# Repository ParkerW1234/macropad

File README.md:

<h1>Hackpad</h1>

<p>
A simple <strong>5-key macropad</strong> built with a <strong>Seeed XIAO RP2040</strong> and a <strong>0.91&quot; OLED display</strong>.
</p>

<p>
Designed as a small, programmable USB macropad.
</p>

<hr>

<h2>Features</h2>

<ul>
  <li>5 mechanical keys (direct GPIO wiring)</li>
  <li>0.91&quot; I²C OLED display</li>
  <li>USB HID keyboard</li>
  <li>Programmable macros</li>
  <li>Custom PCB (KiCad)</li>
</ul>

<hr>

<h2>Hardware</h2>

<ul>
  <li>Seeed XIAO RP2040</li>
  <li>5× MX-style switches</li>
  <li>0.91&quot; OLED display (GND–VCC–SCL–SDA pin order)</li>
  <li>M3x5mx4mm heatset inserts</li>
  <li>M3x16mm screws</li>
</ul>

<hr>

<h2>Firmware</h2>

<ul>
  <li>Written in CircuitPython</li>
  <li>Acts as a USB keyboard</li>
  <li>Displays simple text/status on the OLED</li>
</ul>

<p>
Main firmware file:
</p>

<pre><code>firmware/main.py</code></pre>

<hr>

<h2>Installation</h2>

<ol>
  <li>Flash CircuitPython to the Seeed XIAO RP2040</li>
  <li>Copy required libraries to <code>CIRCUITPY/lib</code></li>
  <li>Copy <code>main.py</code> to the board</li>
</ol>

<hr>

<h2>PCB</h2>

<ul>
  <li>Designed in KiCad</li>
  <li>Keys wired directly to GPIO pins</li>
  <li>OLED connected over I²C (SDA/SCL)</li>
</ul>

<hr>

<h2>Case</h2>

<p>
The PCB fits inside a simple case that is secured with the M3x5mx4mm heatset inserts and m3x16 mm screws.

<hr>

<h2>My PCB</h2>

<hr>

<h2>My Schematic</h2>

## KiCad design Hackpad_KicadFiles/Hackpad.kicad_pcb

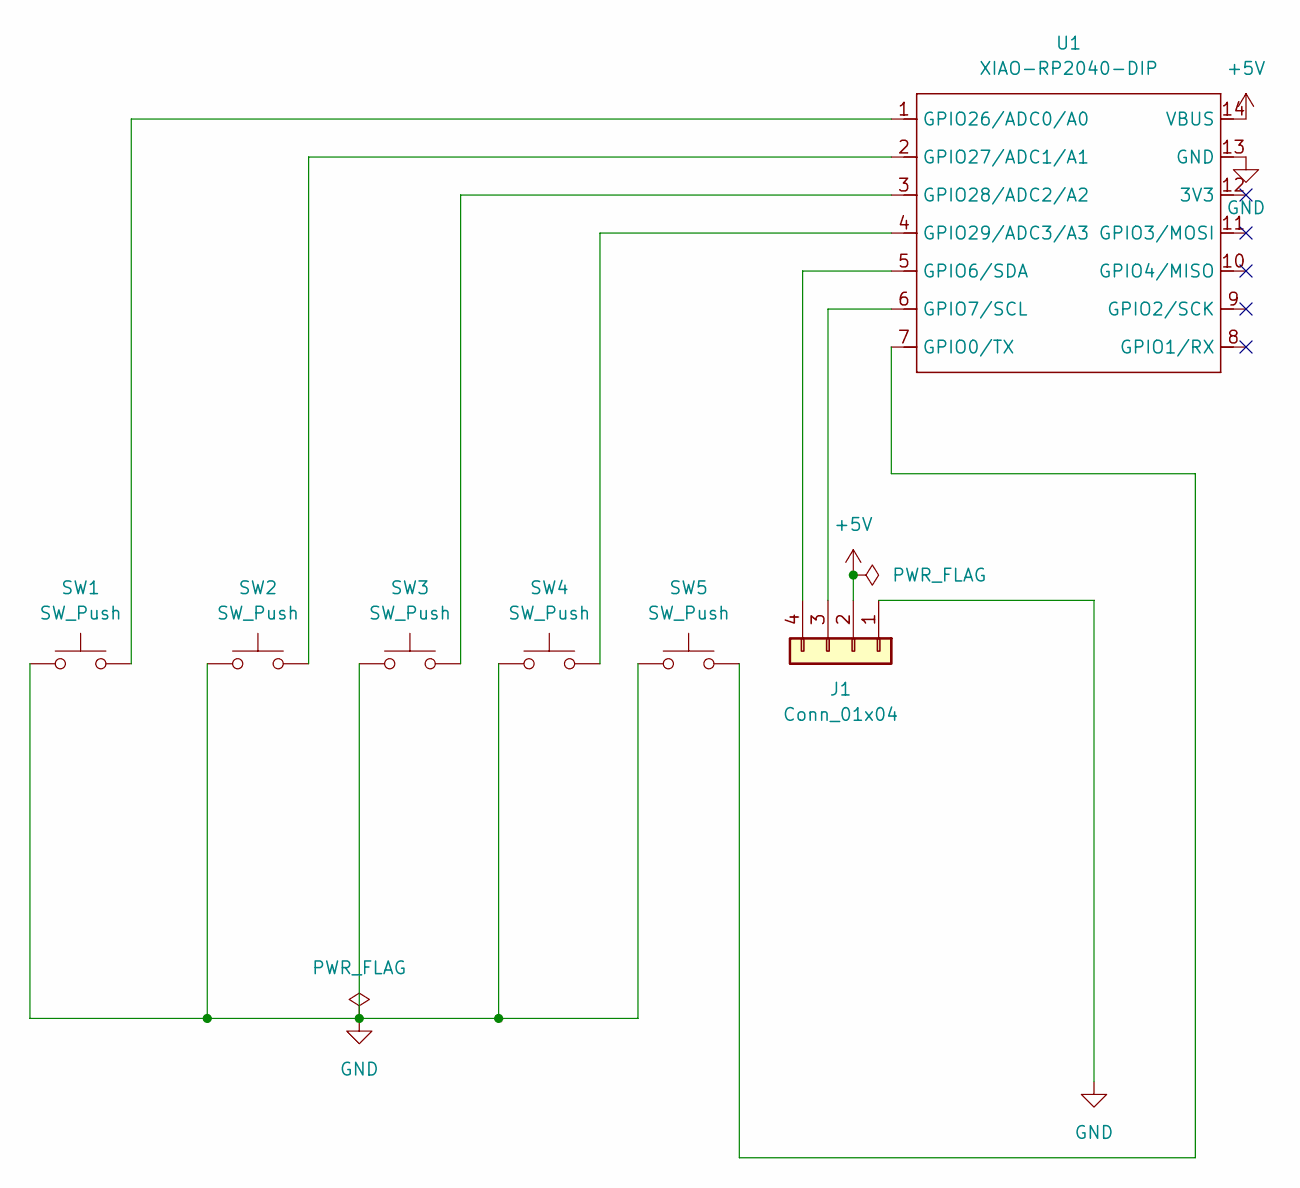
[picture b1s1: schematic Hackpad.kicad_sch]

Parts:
J1: Conn_01x04; PinSocket_1x04_P2.54mm_Vertical
SW1, SW2, SW3, SW4, SW5: SW_Push; SW_Cherry_MX_1.00u_PCB
U1: XIAO-RP2040-DIP; XIAO-ESP32C3-DIP

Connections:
+5V: J1.2, U1.14 (VBUS)
GND: J1.1, SW1.1, SW2.1, SW3.1, SW4.1, SW5.1, U1.13 (GND)
unnamed: J1.3, U1.6 (GPIO7/SCL)
unnamed: J1.4, U1.5 (GPIO6/SDA)
unnamed: SW5.2, U1.7 (GPIO0/TX)
unnamed: SW1.2, U1.1 (GPIO26/ADC0/A0)
unnamed: SW2.2, U1.2 (GPIO27/ADC1/A1)
unnamed: SW3.2, U1.3 (GPIO28/ADC2/A2)
unnamed: SW4.2, U1.4 (GPIO29/ADC3/A3)

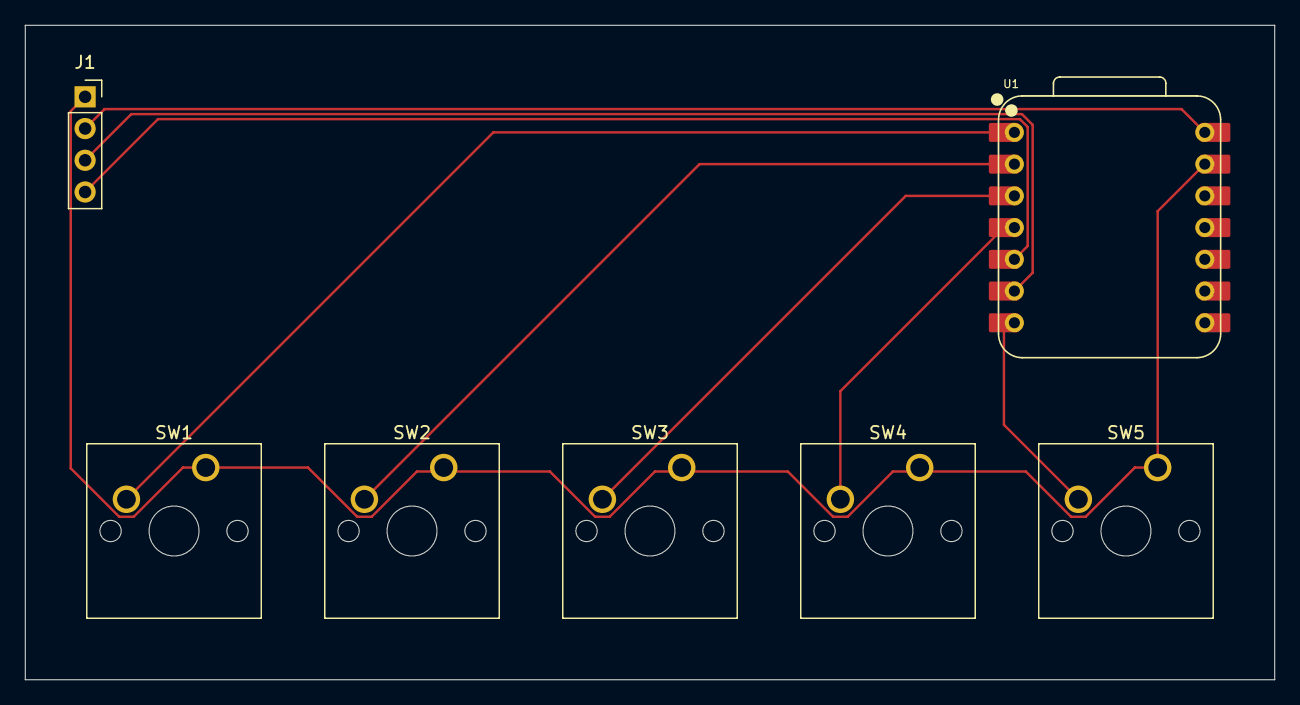
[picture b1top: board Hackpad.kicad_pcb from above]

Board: 2 copper layers, 100.0 x 52.4 mm, 7 parts (0 on the bottom side), 9 nets.

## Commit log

2025-12-27 Rename Hackpad.stl to Hackpad_Bottom.stl
